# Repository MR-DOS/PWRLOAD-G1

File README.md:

# PWRLOAD-G1
DC constant current / constant power digitally controlled load, bachelor thesis in 2017

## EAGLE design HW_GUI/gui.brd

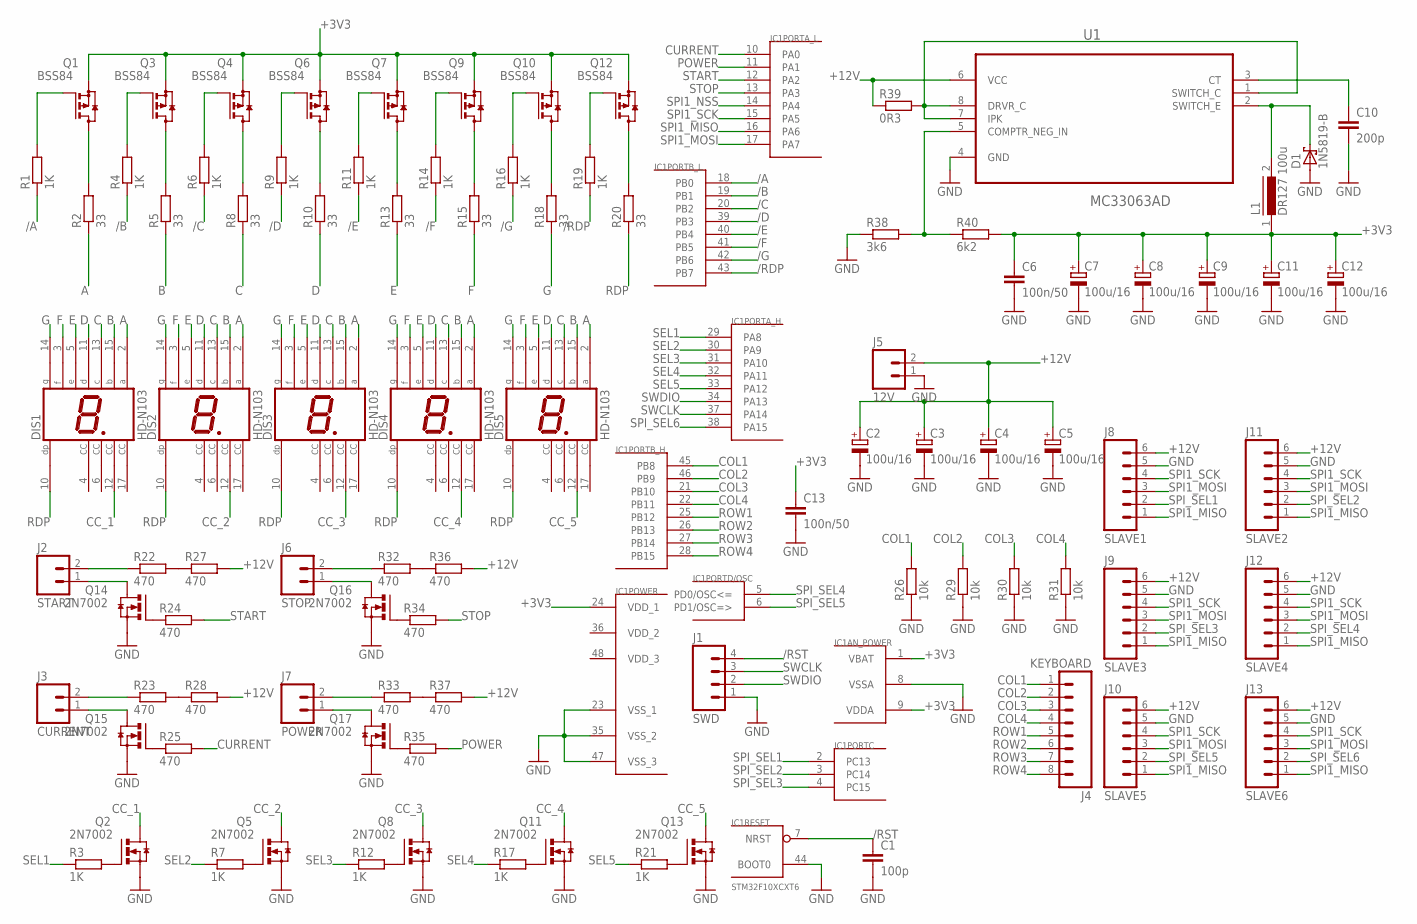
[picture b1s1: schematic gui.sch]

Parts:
C1: 100p; C0805
C2, C3, C4, C5, C7, C8, C9, C11, C12: 100u/16; 153CLV-0605
C6, C13: 100n/50; C0805
C10: 200p; C0805
D1: 1N5819-B; DO41-7.6
DIS1, DIS2, DIS3, DIS4, DIS5: HD-N103; HDSP-Q
IC1: STM32F10XCXT6; TQFP48
J1: SWD; 1X04_SMD_STRAIGHT_COMBO
J2: START; MOLEX-1X2_LOCK
J3: CURRENT; MOLEX-1X2_LOCK
J4: KEYBOARD; 1X08_LOCK_LONGPADS
J5: 12V; MOLEX-1X2_LOCK
J6: STOP; MOLEX-1X2_LOCK
J7: POWER; MOLEX-1X2_LOCK
J8: SLAVE1; MOLEX-1X6_LOCK
J9: SLAVE3; MOLEX-1X6_LOCK
J10: SLAVE5; MOLEX-1X6_LOCK
J11: SLAVE2; MOLEX-1X6_LOCK
J12: SLAVE4; MOLEX-1X6_LOCK
J13: SLAVE6; MOLEX-1X6_LOCK
L1: DR127 100u; DR127
Q1, Q3, Q4, Q6, Q7, Q9, Q10, Q12: BSS84; SOT23
Q2, Q5, Q8, Q11, Q13, Q14, Q15, Q16, Q17: 2N7002; SOT23-BEC
R1, R3, R4, R6, R7, R9, R11, R12, R14, R16, R17, R19, R21: 1K; R0805
R2, R5, R8, R10, R13, R15, R18, R20: 33; R0805
R22, R23, R24, R25, R27, R28, R32, R33, R34, R35, R36, R37: 470; R0805
R26, R29, R30, R31: 10k; R0805
R38: 3k6; R0805
R39: 0R3; R0805
R40: 6k2; R0805
U1: MC33063AD; SOIC127P600X175-8N

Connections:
+3V3: C6.1, C7.+, C8.+, C9.+, C11.+, C12.+, C13.1, IC1.1 (VBAT), IC1.9 (VDDA), IC1.24 (VDD_1), L1.1, Q1.2 (S), Q3.2 (S), Q4.2 (S), Q6.2 (S), Q7.2 (S), Q9.2 (S), Q10.2 (S), Q12.2 (S), R40.2
+12V: C2.+, C3.+, C4.+, C5.+, J5.2, J8.6, J9.6, J10.6, J11.6, J12.6, J13.6, R27.2, R28.2, R36.2, R37.2, R39.1, U1.6 (VCC)
/A: IC1.18 (PB0), R1.1
/B: IC1.19 (PB1), R4.1
/C: IC1.20 (PB2), R6.1
/D: IC1.39 (PB3), R9.1
/E: IC1.40 (PB4), R11.1
/F: IC1.41 (PB5), R14.1
/G: IC1.42 (PB6), R16.1
/RDP: IC1.43 (PB7), R19.1
/RST: C1.1, IC1.7 (NRST), J1.4
A: DIS1.2 (A), DIS2.2 (A), DIS3.2 (A), DIS4.2 (A), DIS5.2 (A), R2.1
B: DIS1.15 (B), DIS2.15 (B), DIS3.15 (B), DIS4.15 (B), DIS5.15 (B), R5.1
C: DIS1.13 (C), DIS2.13 (C), DIS3.13 (C), DIS4.13 (C), DIS5.13 (C), R8.1
CC_1: DIS1.12 (CC), Q2.C (D)
CC_2: DIS2.12 (CC), Q5.C (D)
CC_3: DIS3.12 (CC), Q8.C (D)
CC_4: DIS4.12 (CC), Q11.C (D)
CC_5: DIS5.12 (CC), Q13.C (D)
COL1: IC1.45 (PB8), J4.1, R26.2
COL2: IC1.46 (PB9), J4.2, R29.2
COL3: IC1.21 (PB10), J4.3, R30.2
COL4: IC1.22 (PB11), J4.4, R31.2
CURRENT: IC1.10 (PA0), R25.2
D: DIS1.11 (D), DIS2.11 (D), DIS3.11 (D), DIS4.11 (D), DIS5.11 (D), R10.1
E: DIS1.5 (E), DIS2.5 (E), DIS3.5 (E), DIS4.5 (E), DIS5.5 (E), R13.1
F: DIS1.3 (F), DIS2.3 (F), DIS3.3 (F), DIS4.3 (F), DIS5.3 (F), R15.1
G: DIS1.14 (G), DIS2.14 (G), DIS3.14 (G), DIS4.14 (G), DIS5.14 (G), R18.1
GND: C1.2, C2.-, C3.-, C4.-, C5.-, C6.2, C7.-, C8.-, C9.-, C10.2, C11.-, C12.-, C13.2, D1.A, IC1.8 (VSSA), IC1.23 (VSS_1), IC1.35 (VSS_2), IC1.44 (BOOT0), IC1.47 (VSS_3), J1.1, J5.1, J8.5, J9.5, J10.5, J11.5, J12.5, J13.5, Q2.E (S), Q5.E (S), Q8.E (S), Q11.E (S), Q13.E (S), Q14.E (S), Q15.E (S), Q16.E (S), Q17.E (S), R26.1, R29.1, R30.1, R31.1, R38.1, U1.4 (GND)
N3: Q8.B (G), R12.2
unnamed: Q1.3 (D), R2.2
unnamed: Q3.3 (D), R5.2
unnamed: Q4.3 (D), R8.2
unnamed: Q6.3 (D), R10.2
unnamed: Q7.3 (D), R13.2
unnamed: Q9.3 (D), R15.2
unnamed: Q10.3 (D), R18.2
unnamed: Q12.3 (D), R20.2
unnamed: Q11.B (G), R17.2
unnamed: Q2.B (G), R3.2
unnamed: Q5.B (G), R7.2
unnamed: Q13.B (G), R21.2
unnamed: Q12.1 (G), R19.2
unnamed: Q10.1 (G), R16.2
unnamed: Q9.1 (G), R14.2
unnamed: Q7.1 (G), R11.2
unnamed: Q6.1 (G), R9.2
unnamed: Q4.1 (G), R6.2
unnamed: Q3.1 (G), R4.2
unnamed: Q1.1 (G), R1.2
unnamed: J3.1, Q15.C (D)
unnamed: J7.1, Q17.C (D)
unnamed: J3.2, R23.1
unnamed: R23.2, R28.1
unnamed: J7.2, R33.1
unnamed: R33.2, R37.1
unnamed: J2.1, Q14.C (D)
unnamed: J2.2, R22.1
unnamed: R22.2, R27.1
unnamed: J6.1, Q16.C (D)
unnamed: J6.2, R32.1
unnamed: R32.2, R36.1
unnamed: R38.2, R40.1, U1.5 (COMPTR_NEG_IN)
unnamed: C10.1, U1.3 (CT)
unnamed: Q14.B (G), R24.1
unnamed: R39.2, U1.1 (SWITCH_C), U1.7 (IPK), U1.8 (DRVR_C)
unnamed: D1.C, L1.2, U1.2 (SWITCH_E)
unnamed: Q15.B (G), R25.1
unnamed: Q16.B (G), R34.1
unnamed: Q17.B (G), R35.1
POWER: IC1.11 (PA1), R35.2
RDP: DIS1.10 (DP), DIS2.10 (DP), DIS3.10 (DP), DIS4.10 (DP), DIS5.10 (DP), R20.1
ROW1: IC1.25 (PB12), J4.5
ROW2: IC1.26 (PB13), J4.6
ROW3: IC1.27 (PB14), J4.7
ROW4: IC1.28 (PB15), J4.8
SEL1: IC1.29 (PA8), R3.1
SEL2: IC1.30 (PA9), R7.1
SEL3: IC1.31 (PA10), R12.1
SEL4: IC1.32 (PA11), R17.1
SEL5: IC1.33 (PA12), R21.1
SPI1_MISO: IC1.16 (PA6), J8.1, J9.1, J10.1, J11.1, J12.1, J13.1
SPI1_MOSI: IC1.17 (PA7), J8.3, J9.3, J10.3, J11.3, J12.3, J13.3
SPI1_NSS: IC1.14 (PA4)
SPI1_SCK: IC1.15 (PA5), J8.4, J9.4, J10.4, J11.4, J12.4, J13.4
SPI_SEL1: IC1.2 (PC13), J8.2
SPI_SEL2: IC1.3 (PC14), J11.2
SPI_SEL3: IC1.4 (PC15), J9.2
SPI_SEL4: IC1.5 (PD0/OSC<=), J12.2
SPI_SEL5: IC1.6 (PD1/OSC=>), J10.2
SPI_SEL6: IC1.38 (PA15), J13.2
START: IC1.12 (PA2), R24.2
STOP: IC1.13 (PA3), R34.2
SWCLK: IC1.37 (PA14), J1.3
SWDIO: IC1.34 (PA13), J1.2
VDD_2: IC1.36 (VDD_2)
VDD_3: IC1.48 (VDD_3)

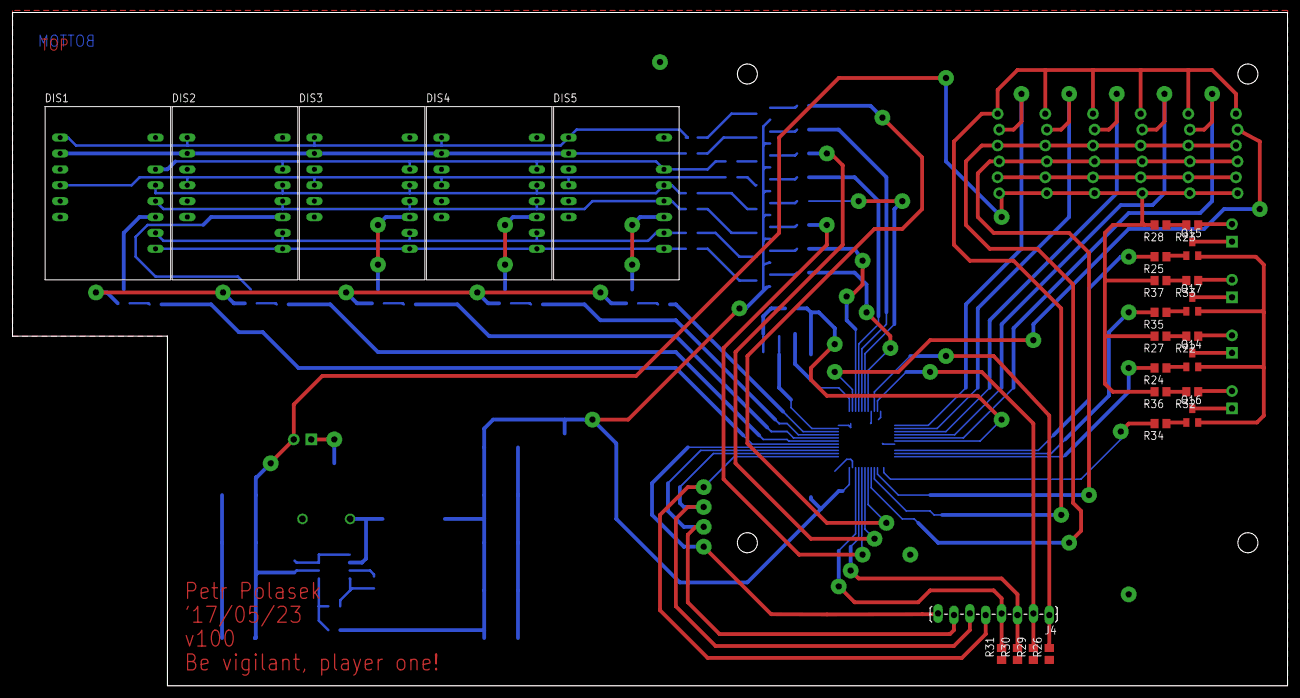
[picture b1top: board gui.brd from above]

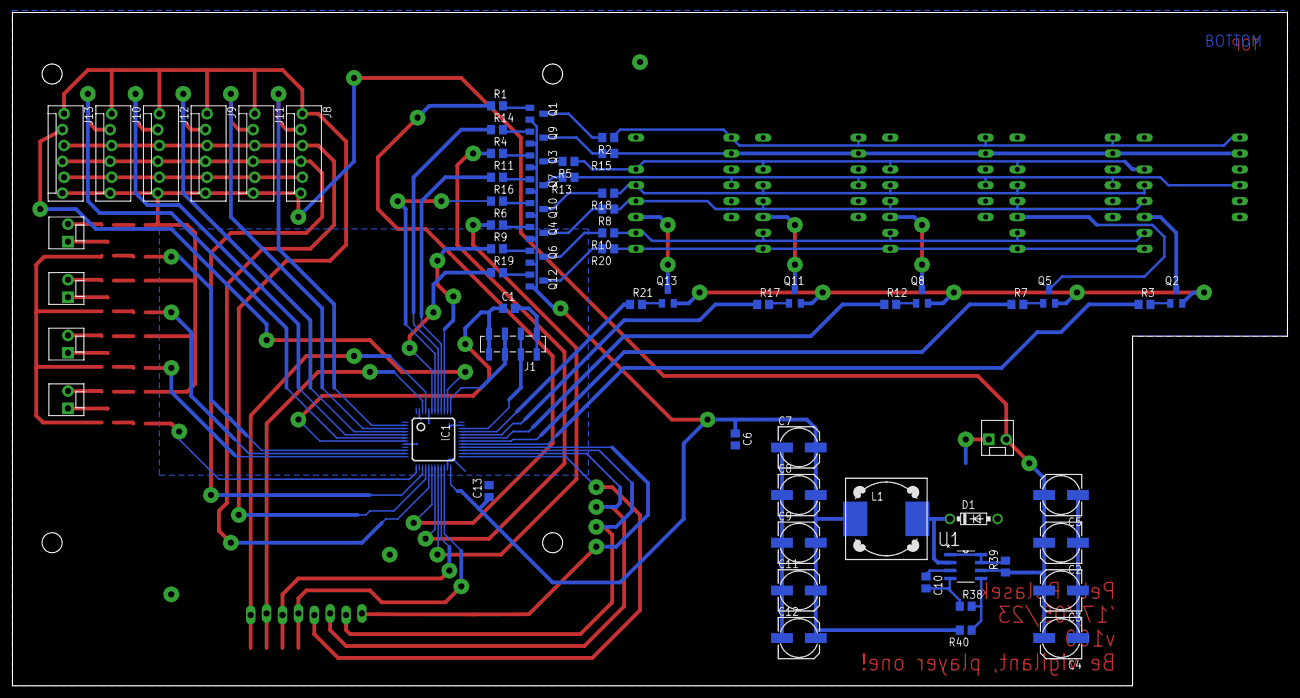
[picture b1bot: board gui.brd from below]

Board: 2 copper layers, 203.8 x 107.6 mm, 92 parts (66 on the bottom side), 94 nets.

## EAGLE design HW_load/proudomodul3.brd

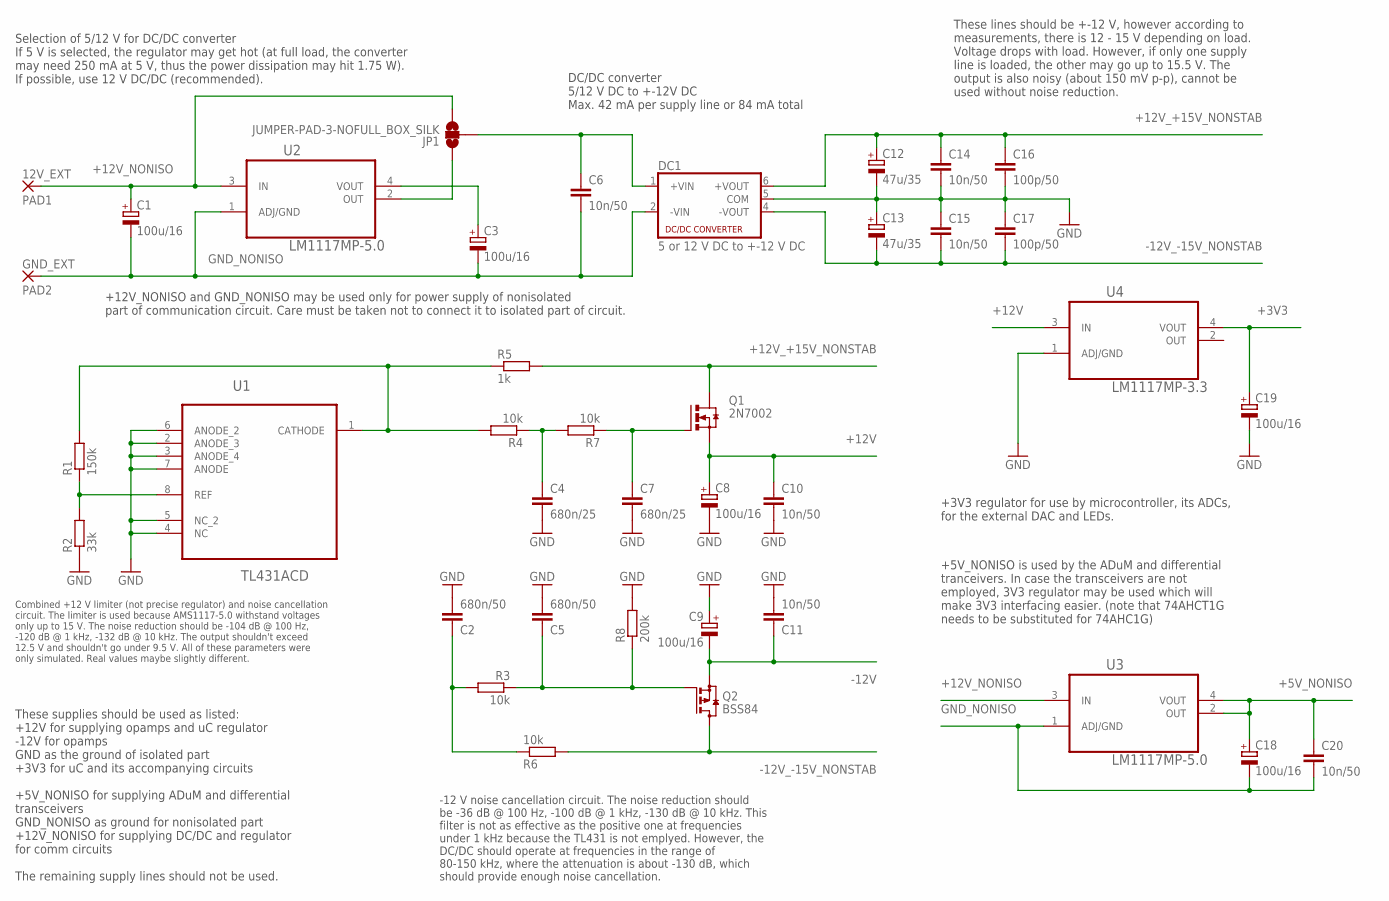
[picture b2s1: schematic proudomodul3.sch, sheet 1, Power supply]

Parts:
C1, C3, C8, C9, C18, C19: 100u/16; 153CLV-0605
C2, C5: 680n/50; C0805
C4, C7: 680n/25; C0805
C6, C10, C11, C14, C15, C20: 10n/50; C0805
C12, C13: 47u/35; 153CLV-0605
C16, C17: 100p/50; C0805
DC1: 5 or 12 V DC to +-12 V DC; NMA
JP1: JUMPER-PAD-3-NOFULL_BOX_SILK; PAD-JUMPER-3-NO_YES_SILK_FULL_BOX
PAD1: 12V_EXT; 2,15/1,0
PAD2: GND_EXT; 2,15/1,0
Q1: 2N7002; SOT23-BEC
Q2: BSS84; SOT23
R1: 150k; R0805
R2: 33k; R0805
R3, R4, R6, R7: 10k; R0805
R5: 1k; R0805
R8: 200k; R0805
U1: TL431ACD; SOIC127P600X175-8N
U2, U3: LM1117MP-5.0; SOT230P696X180-4N
U4: LM1117MP-3.3; SOT230P696X180-4N

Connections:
+3V3: C19.+, U4.4 (VOUT); also elsewhere on the board
+5V_NONISO: C18.+, C20.1, U3.2 (OUT), U3.4 (VOUT); also elsewhere on the board
+12V: C8.+, C10.1, Q1.E (S), U4.3 (IN); also elsewhere on the board
+12V_+15V_NONSTAB: C12.+, C14.1, C16.1, DC1.6 (+VOUT), Q1.C (D), R5.2
+12V_NONISO: C1.+, JP1.3, PAD1.1, U2.3 (IN), U3.3 (IN); also elsewhere on the board
-12V: C9.-, C11.1, Q2.2 (S); also elsewhere on the board
-12V_-15V_NONSTAB: C13.-, C15.2, C17.2, DC1.4 (-VOUT), Q2.3 (D), R6.2
GND: C2.2, C4.2, C5.2, C7.2, C8.-, C9.+, C10.2, C11.2, C12.-, C13.+, C14.2, C15.1, C16.2, C17.1, C19.-, DC1.5 (COM), R2.1, R8.2, U1.2 (ANODE_3), U1.3 (ANODE_4), U1.4 (NC), U1.5 (NC_2), U1.6 (ANODE_2), U1.7 (ANODE), U4.1 (ADJ/GND); also elsewhere on the board
GND_NONISO: C1.-, C3.-, C6.2, C18.-, C20.2, DC1.2 (-VIN), PAD2.1, U2.1 (ADJ/GND), U3.1 (ADJ/GND); also elsewhere on the board
unnamed: C4.1, R4.1, R7.2
unnamed: C6.1, DC1.1 (+VIN), JP1.2
unnamed: R1.1, R2.2, U1.8 (REF)
unnamed: R1.2, R4.2, R5.1, U1.1 (CATHODE)
unnamed: C7.1, Q1.B (G), R7.1
unnamed: C2.1, R3.2, R6.1
unnamed: C5.1, Q2.1 (G), R3.1, R8.1
unnamed: JP1.1, U2.2 (OUT)
unnamed: C3.+, U2.4 (VOUT)

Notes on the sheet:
DC/DC converter 5/12 V DC to +-12V DC Max. 42 mA per supply line or 84 mA total
Selection of 5/12 V for DC/DC converter If 5 V is selected, the regulator may get hot (at full load, the converter may need 250 mA at 5 V, thus the power dissipation may hit 1.75 W). If possible, use 12 V DC/DC (recommended).
These lines should be +-12 V, however according to measurements, there is 12 - 15 V depending on load. Voltage drops with load. However, if only one supply line is loaded, the other may go up to 15.5 V. The output is also noisy (about 150 mV p-p), cannot be used without noise reduction.
Combined +12 V limiter (not precise regulator) and noise cancellation circuit. The limiter is used because AMS1117-5.0 withstand voltages only up to 15 V. The noise reduction should be -104 dB @ 100 Hz, -120 dB @ 1 kHz, -132 dB @ 10 kHz. The output shouldn't exceed 12.5 V and shouldn't go under 9.5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
-12 V noise cancellation circuit. The noise reduction should be -36 dB @ 100 Hz, -100 dB @ 1 kHz, -130 dB @ 10 kHz. This filter is not as effective as the positive one at frequencies under 1 kHz because the TL431 is not emplyed. However, the DC/DC should operate at frequencies in the range of 80-15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
+12V_NONISO and GND_NONISO may be used only for power supply of nonisolated part of communication circuit. Care must be taken not to connect it to isolated part of circuit.
+3V3 regulator for use by microcontroller, its ADCs, for the external DAC and LEDs.
These supplies should be used as listed: +12V for supplying opamps and uC regulator -12V for opamps GND as the ground of isolated part +3V3 for uC and its accompanying circuits +5V_NONISO for supplying ADuM and differential transceivers GND_NONISO as ground for nonisolated part +12V_NONISO for supp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
+5V_NONISO is used by the ADuM and differential tranceivers. In case the transceivers are not employed, 3V3 regulator may be used which will make 3V3 interfacing easier. (note that 74AHCT1G needs to be substituted for 74AHC1G)

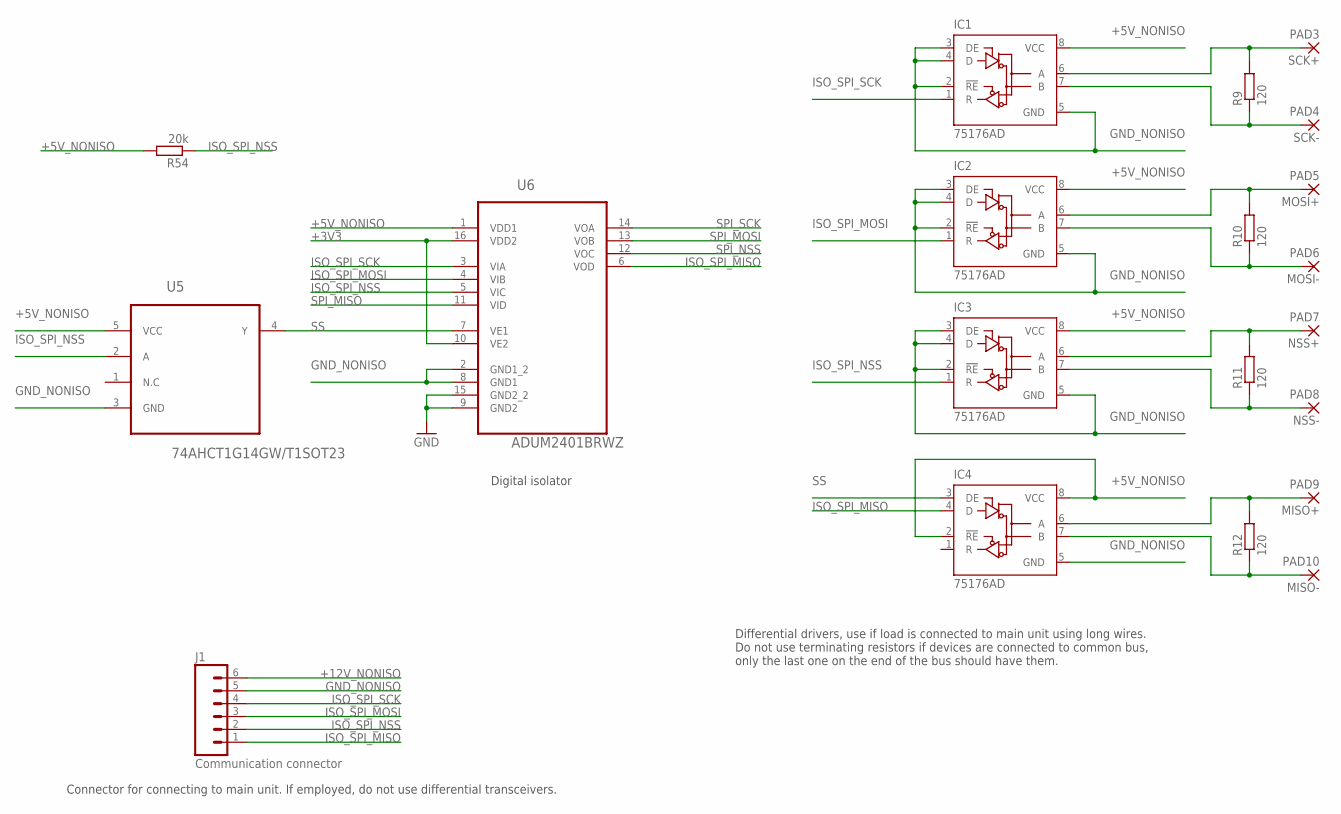
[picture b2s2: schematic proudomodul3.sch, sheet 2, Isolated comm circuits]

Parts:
IC1, IC2, IC3, IC4: 75176AD; D_R-PDSO-G8
J1: Communication connector; MOLEX-1X6-RA_LOCK
PAD3: SCK+; 2,15/1,0
PAD4: SCK-; 2,15/1,0
PAD5: MOSI+; 2,15/1,0
PAD6: MOSI-; 2,15/1,0
PAD7: NSS+; 2,15/1,0
PAD8: NSS-; 2,15/1,0
PAD9: MISO+; 2,15/1,0
PAD10: MISO-; 2,15/1,0
R9, R10, R11, R12: 120; R0805
R54: 20k; R0805
U5: 74AHCT1G14GW/T1SOT23; SOT23-5L
U6: ADUM2401BRWZ; SOIC127P1032X265-16N

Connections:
+3V3: U6.10 (VE2), U6.16 (VDD2); also elsewhere on the board
+5V_NONISO: IC1.8 (VCC), IC2.8 (VCC), IC3.8 (VCC), IC4.2 (!RE), IC4.8 (VCC), R54.2, U5.5 (VCC), U6.1 (VDD1); also elsewhere on the board
+12V_NONISO: J1.6; also elsewhere on the board
GND: U6.9 (GND2), U6.15 (GND2_2); also elsewhere on the board
GND_NONISO: IC1.2 (!RE), IC1.3 (DE), IC1.4 (D), IC1.5 (GND), IC2.2 (!RE), IC2.3 (DE), IC2.4 (D), IC2.5 (GND), IC3.2 (!RE), IC3.3 (DE), IC3.4 (D), IC3.5 (GND), IC4.5 (GND), J1.5, U5.3 (GND), U6.2 (GND1_2), U6.8 (GND1); also elsewhere on the board
ISO_SPI_MISO: IC4.4 (D), J1.1, U6.6 (VOD)
ISO_SPI_MOSI: IC2.1 (R), J1.3, U6.4 (VIB)
ISO_SPI_NSS: IC3.1 (R), J1.2, R54.1, U5.2 (A), U6.5 (VIC)
ISO_SPI_SCK: IC1.1 (R), J1.4, U6.3 (VIA)
unnamed: IC4.6 (A), PAD9.1, R12.2
unnamed: IC4.7 (B), PAD10.1, R12.1
unnamed: IC3.6 (A), PAD7.1, R11.2
unnamed: IC3.7 (B), PAD8.1, R11.1
unnamed: IC2.6 (A), PAD5.1, R10.2
unnamed: IC2.7 (B), PAD6.1, R10.1
unnamed: IC1.7 (B), PAD4.1, R9.1
unnamed: IC1.6 (A), PAD3.1, R9.2
SPI_MISO: U6.11 (VID); also elsewhere on the board
SPI_MOSI: U6.13 (VOB); also elsewhere on the board
SPI_NSS: U6.12 (VOC); also elsewhere on the board
SPI_SCK: U6.14 (VOA); also elsewhere on the board
SS: IC4.3 (DE), U5.4 (Y), U6.7 (VE1)

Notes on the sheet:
Differential drivers, use if load is connected to main unit using long wires. Do not use terminating resistors if devices are connected to common bus, only the last one on the end of the bus should have them.
Digital isolator
Connector for connecting to main unit. If employed, do not use differential transceivers.

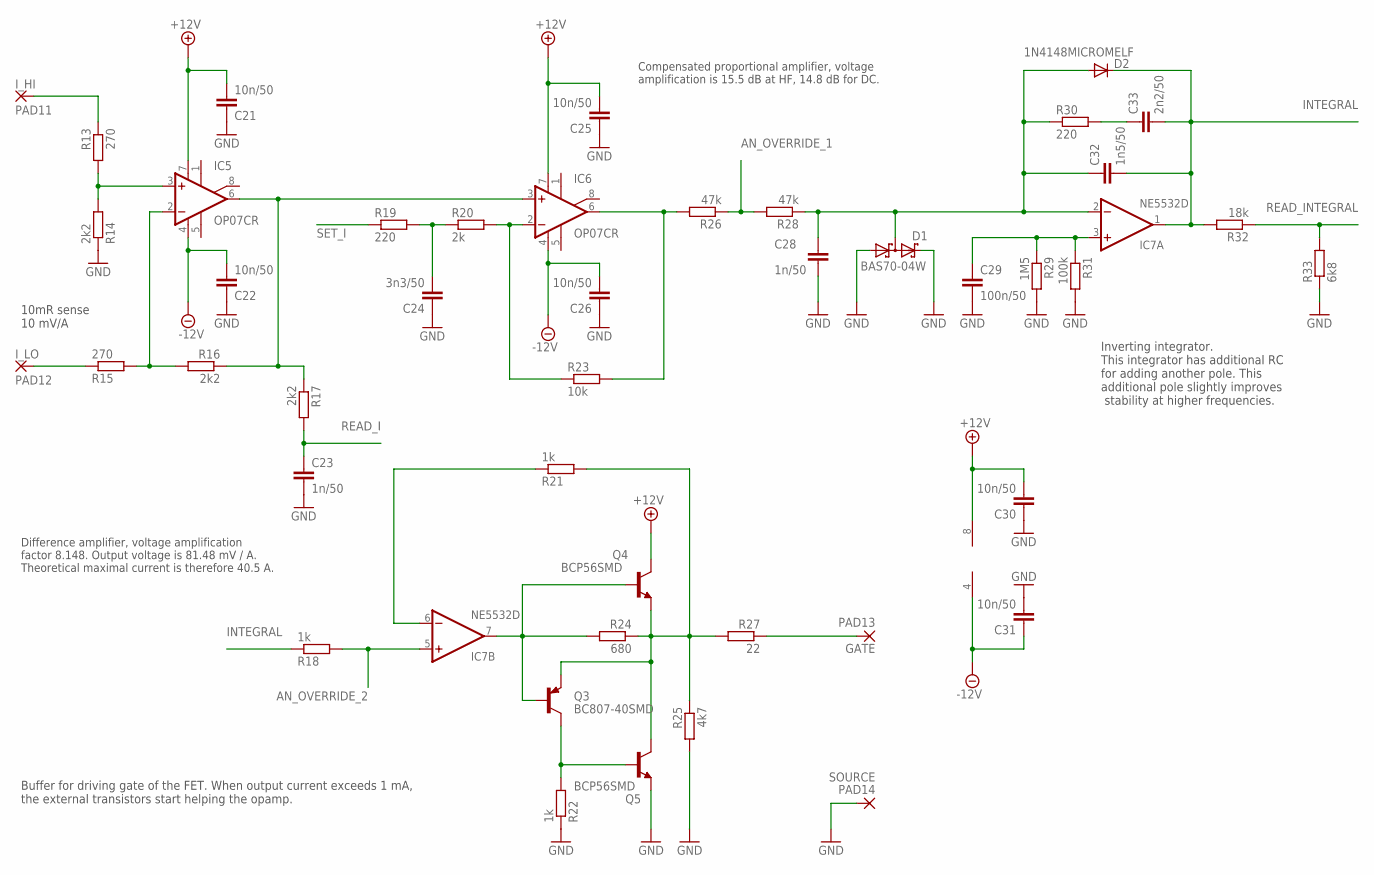
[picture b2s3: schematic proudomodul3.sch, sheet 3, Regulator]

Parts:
C21, C22, C25, C26, C30, C31: 10n/50; C0805
C23, C28: 1n/50; C0805
C24: 3n3/50; C0805
C29: 100n/50; C0805
C32: 1n5/50; C0805
C33: 2n2/50; C0805
D1: BAS70-04W; SOT323
D2: 1N4148MICROMELF; MICROMELF-W
IC5, IC6: OP07CR; SO08
IC7: NE5532D; SO08
PAD11: I_HI; 2,15/1,0
PAD12: I_LO; 2,15/1,0
PAD13: GATE; 2,15/1,0
PAD14: SOURCE; 2,15/1,0
Q3: BC807-40SMD; SOT23-BEC
Q4, Q5: BCP56SMD; SOT223
R13, R15: 270; R0805
R14, R16, R17: 2k2; R0805
R18, R21, R22: 1k; R0805
R19, R30: 220; R0805
R20: 2k; R0805
R23: 10k; R0805
R24: 680; R0805
R25: 4k7; R0805
R26, R28: 47k; R0805
R27: 22; R0805
R29: 1M5; R0805
R31: 100k; R0805
R32: 18k; R0805
R33: 6k8; R0805

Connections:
+12V: C21.2, C25.2, C30.2, IC5.7 (V+), IC6.7 (V+), IC7.8 (V+), Q4.2 (C), Q4.4 (C); also elsewhere on the board
-12V: C22.2, C26.2, C31.1, IC5.4 (V-), IC6.4 (V-), IC7.4 (V-); also elsewhere on the board
AN_OVERRIDE_1: R26.1, R28.2; also elsewhere on the board
AN_OVERRIDE_2: IC7.5 (+IN), R18.2; also elsewhere on the board
GND: C21.1, C22.1, C23.2, C24.1, C25.1, C26.1, C28.2, C29.2, C30.1, C31.2, D1.1 (A1), D1.2 (C2), PAD14.1, Q5.3 (E), R14.1, R22.1, R25.2, R29.2, R31.2, R33.1; also elsewhere on the board
INTEGRAL: C32.2, C33.2, D2.C, IC7.1 (OUT), R18.1, R32.2
unnamed: C33.1, R30.2
unnamed: PAD11.1, R13.1
unnamed: PAD13.1, R27.1
unnamed: Q3.E, Q4.3 (E), Q5.2 (C), Q5.4 (C), R21.2, R24.1, R25.1, R27.2
unnamed: IC7.7 (OUT), Q3.B, Q4.1 (B), R24.2
unnamed: IC5.3 (+IN), R13.2, R14.2
unnamed: PAD12.1, R15.1
unnamed: IC5.2 (-IN), R15.2, R16.2
unnamed: C28.1, C32.1, D1.3 (C1A2), D2.A, IC7.2 (-IN), R28.1, R30.1
unnamed: C29.1, IC7.3 (+IN), R29.1, R31.1
unnamed: IC6.6 (OUT), R23.2, R26.2
unnamed: Q3.C, Q5.1 (B), R22.2
unnamed: IC7.6 (-IN), R21.1
unnamed: IC6.2 (-IN), R20.2, R23.1
unnamed: IC5.6 (OUT), IC6.3 (+IN), R16.1, R17.1
unnamed: C24.2, R19.2, R20.1
READ_I: C23.1, R17.2; also elsewhere on the board
READ_INTEGRAL: R32.1, R33.2; also elsewhere on the board
SET_I: R19.1; also elsewhere on the board

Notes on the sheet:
10mR sense 10 mV/A
Compensated proportional amplifier, voltage amplification is 15.5 dB at HF, 14.8 dB for DC.
Inverting integrator. This integrator has additional RC for adding another pole. This additional pole slightly improves stability at higher frequencies.
Buffer for driving gate of the FET. When output current exceeds 1 mA, the external transistors start helping the opamp.
Difference amplifier, voltage amplification factor 8.148. Output voltage is 81.48 mV / A. Theoretical maximal current is therefore 40.5 A.

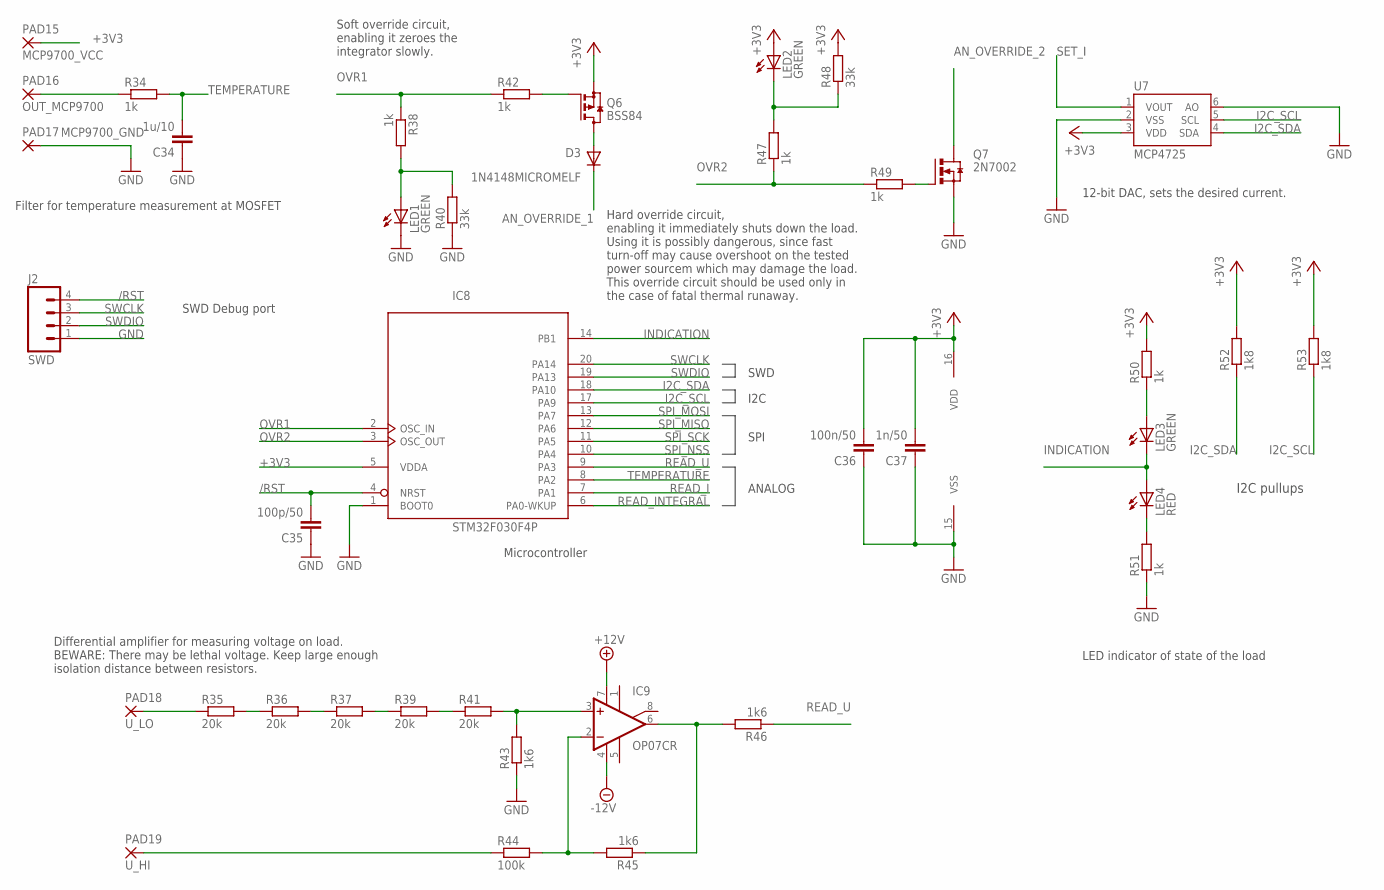
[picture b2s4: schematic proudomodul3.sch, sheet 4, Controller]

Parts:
C34: 1u/10; C0805
C35: 100p/50; C0805
C36: 100n/50; C0805
C37: 1n/50; C0805
D3: 1N4148MICROMELF; MICROMELF-W
IC8: STM32F030F4P; TSSOP20-I
IC9: OP07CR; SO08
J2: SWD; 1X04_SMD_STRAIGHT_COMBO
LED1, LED2, LED3: GREEN; SML0603
LED4: RED; SML0603
PAD15: MCP9700_VCC; 2,15/1,0
PAD16: OUT_MCP9700; 2,15/1,0
PAD17: MCP9700_GND; 2,15/1,0
PAD18: U_LO; 2,15/1,0
PAD19: U_HI; 2,15/1,0
Q6: BSS84; SOT23
Q7: 2N7002; SOT23-BEC
R34, R38, R42, R47, R49, R50, R51: 1k; R0805
R35, R36, R37, R39, R41: 20k; R0805
R40, R48: 33k; R0805
R43, R45, R46: 1k6; R0805
R44: 100k; R0805
R52, R53: 1k8; R0805
U7: MCP4725; SOT23-6

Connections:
+3V3: C36.2, C37.2, IC8.5 (VDDA), IC8.16 (VDD), LED2.A, PAD15.1, Q6.2 (S), R48.2, R50.2, R52.2, R53.2, U7.3 (VDD); also elsewhere on the board
+12V: IC9.7 (V+); also elsewhere on the board
-12V: IC9.4 (V-); also elsewhere on the board
/RST: C35.2, IC8.4 (NRST), J2.4
AN_OVERRIDE_1: D3.C; also elsewhere on the board
AN_OVERRIDE_2: Q7.C (D); also elsewhere on the board
GND: C34.1, C35.1, C36.1, C37.1, IC8.1 (BOOT0), IC8.15 (VSS), J2.1, LED1.C, PAD17.1, Q7.E (S), R40.1, R43.1, R51.1, U7.2 (VSS), U7.6 (AO); also elsewhere on the board
I2C_SCL: IC8.17 (PA9), R53.1, U7.5 (SCL)
I2C_SDA: IC8.18 (PA10), R52.1, U7.4 (SDA)
INDICATION: IC8.14 (PB1), LED3.C, LED4.A
unnamed: LED1.A, R38.2, R40.2
unnamed: Q6.1 (G), R42.2
unnamed: Q7.B (G), R49.2
unnamed: D3.A, Q6.3 (D)
unnamed: LED2.C, R47.2, R48.1
unnamed: PAD16.1, R34.1
unnamed: IC9.3 (+IN), R41.2, R43.2
unnamed: LED3.A, R50.1
unnamed: IC9.2 (-IN), R44.2, R45.2
unnamed: IC9.6 (OUT), R45.1, R46.2
unnamed: R39.2, R41.1
unnamed: R37.2, R39.1
unnamed: R36.2, R37.1
unnamed: R35.2, R36.1
unnamed: PAD19.1, R44.1
unnamed: PAD18.1, R35.1
unnamed: LED4.C, R51.2
OVR1: IC8.2 (OSC_IN), R38.1, R42.1
OVR2: IC8.3 (OSC_OUT), R47.1, R49.1
READ_I: IC8.7 (PA1); also elsewhere on the board
READ_INTEGRAL: IC8.6 (PA0-WKUP); also elsewhere on the board
READ_U: IC8.9 (PA3), R46.1
SET_I: U7.1 (VOUT); also elsewhere on the board
SPI_MISO: IC8.12 (PA6); also elsewhere on the board
SPI_MOSI: IC8.13 (PA7); also elsewhere on the board
SPI_NSS: IC8.10 (PA4); also elsewhere on the board
SPI_SCK: IC8.11 (PA5); also elsewhere on the board
SWCLK: IC8.20 (PA14), J2.3
SWDIO: IC8.19 (PA13), J2.2
TEMPERATURE: C34.2, IC8.8 (PA2), R34.2

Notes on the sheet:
I2C
SWD
SPI
ANALOG
Filter for temperature measurement at MOSFET
Soft override circuit, enabling it zeroes the integrator slowly.
Hard override circuit, enabling it immediately shuts down the load. Using it is possibly dangerous, since fast turn-off may cause overshoot on the tested power sourcem which may damage the load. This override circuit should be used only in the case of fatal thermal runaway.
12-bit DAC, sets the desired current.
SWD Debug port
I2C pullups
Differential amplifier for measuring voltage on load. BEWARE: There may be lethal voltage. Keep large enough isolation distance between resistors.
Microcontroller
LED indicator of state of the load

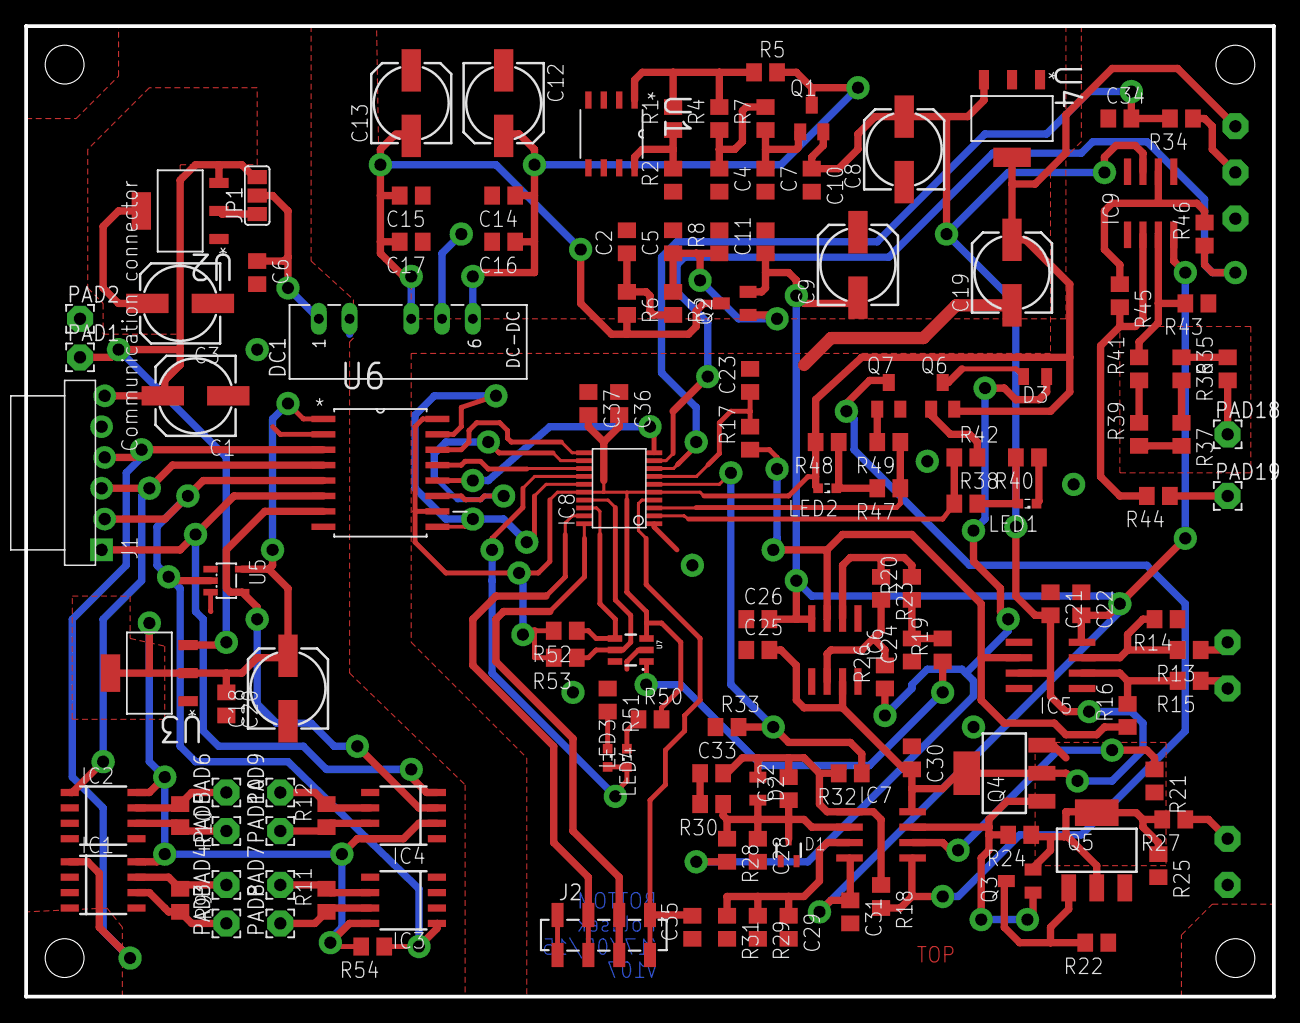
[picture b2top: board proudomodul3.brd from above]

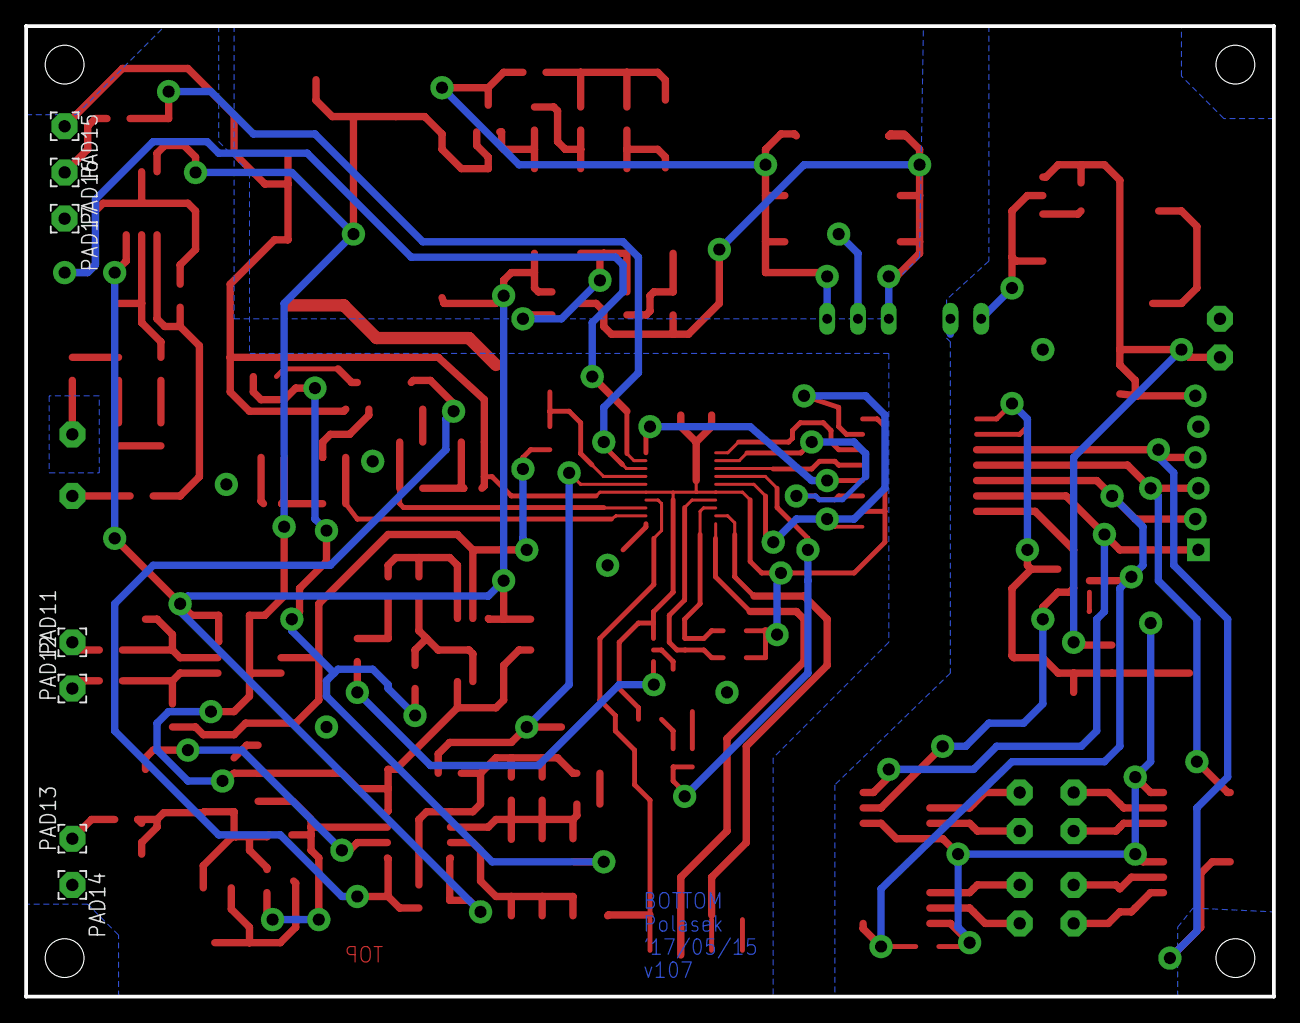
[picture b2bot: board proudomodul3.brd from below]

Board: 2 copper layers, 102.9 x 80.0 mm, 143 parts (7 on the bottom side), 84 nets.

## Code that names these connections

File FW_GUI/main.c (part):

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
#define		digit_pins		(nA_pin | nB_pin | nC_pin | nD_pin | nE_pin | nF_pin | nG_pin | nRDP_pin)

#define		SEL1					GPIO_Pin_8
#define		SEL2					GPIO_Pin_9
#define		SEL3					GPIO_Pin_10
#define		SEL4					GPIO_Pin_11
#define		SEL5					GPIO_Pin_12

#define		select_pins		(SEL1 | SEL2 | SEL3 | SEL4 | SEL5)

#define		CURRENT_pin		GPIO_Pin_0
#define		POWER_pin			GPIO_Pin_1
#define		START_pin			GPIO_Pin_2
#define		STOP_pin			GPIO_Pin_3

#define		MODE_pins			(CURRENT_pin | POWER_pin)
#define		STATE_pins		(START_pin 	 | STOP_pin)
#define		LED_pins			(CURRENT_pin | POWER_pin | START_pin | STOP_pin)

#define		COL1					GPIO_Pin_8
#define		COL2					GPIO_Pin_9
#define		COL3					GPIO_Pin_10
#define		COL4					GPIO_Pin_11

#define		COLUMN_pins	  (COL1 | COL2 | COL3 | COL4)

#define		ROW1					GPIO_Pin_12
#define		ROW2					GPIO_Pin_13
#define		ROW3					GPIO_Pin_14
#define		ROW4					GPIO_Pin_15

#define		ROW_pins			(ROW1 | ROW2 | ROW3 | ROW4)

#define		KEYPAD_pins		(COLUMN_pins | ROW_pins)

#define		SPI_SCK_pin		GPIO_Pin_5
#define		SPI_MISO_pin	GPIO_Pin_6
#define		SPI_MOSI_pin	GPIO_Pin_7
#define		SPI_SEL2_pin	GPIO_Pin_13
#define		SPI_SEL3_pin	GPIO_Pin_15

#define		SPI_pins			(SPI_SCK_pin | SPI_MISO_pin | SPI_MOSI_pin)
#define		SPI_SEL_pins	(SPI_SEL2_pin | SPI_SEL3_pin)

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	GPIO_SetBits(GPIOB, digit_pins);
	
	GPIO_InitStruct.GPIO_Mode=GPIO_Mode_Out_PP;
	GPIO_InitStruct.GPIO_Pin = SEL1 | SEL2 | SEL3 | SEL4 | SEL5;
	GPIO_InitStruct.GPIO_Speed=GPIO_Speed_10MHz;
	GPIO_Init(GPIOA, &GPIO_InitStruct);	
	
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void ShowLEDs(void)
{
	GPIO_ResetBits(GPIOA, MODE_pins);
	GPIO_SetBits(GPIOA, (load_mode==const_i) ? CURRENT_pin : POWER_pin);
	
	GPIO_ResetBits(GPIOA, STATE_pins);
	GPIO_SetBits(GPIOA, (load_state==DISABLE) ? STOP_pin : START_pin);
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{
	GPIO_SetBits(GPIOB, digit_pins & (~(uint32_t) digit_segments[digit]));
	GPIO_ResetBits(GPIOB, (uint32_t) digit_segments[digit]);
	if (RDP==ENABLE) GPIO_ResetBits(GPIOB, nRDP_pin);
}

void SelectDigit(uint8_t digit)
{
	GPIO_ResetBits(GPIOA, select_pins);
	GPIO_SetBits(GPIOA, SEL5 >> digit);
}

void SPIInit(void)
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	SPI_InitTypeDef	SPI_InitStruct;
	
	GPIO_InitStruct.GPIO_Mode=GPIO_Mode_AF_PP;
	GPIO_InitStruct.GPIO_Pin = SPI_SCK_pin | SPI_MOSI_pin;
	GPIO_InitStruct.GPIO_Speed = GPIO_Speed_50MHz;
	GPIO_Init(GPIOA, &GPIO_InitStruct);	
	
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	GPIO_SetBits(GPIOC, SPI_SEL_pins);
	
	GPIO_InitStruct.GPIO_Mode = GPIO_Mode_IN_FLOATING;	
	GPIO_InitStruct.GPIO_Pin = SPI_MISO_pin;
	GPIO_Init(GPIOA, &GPIO_InitStruct);	
	
	SPI_StructInit(&SPI_InitStruct);
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	if (load_state==DISABLE) temp_cmd=0;
	while (SPI_I2S_GetFlagStatus(SPI1, SPI_I2S_FLAG_BSY)) {};
		
	GPIO_ResetBits(GPIOC, SPI_SEL3_pin);
	for (uint16_t tmp=0; tmp<50; tmp++) {}
	SPI_I2S_SendData(SPI1, temp_cmd);
	while (SPI_I2S_GetFlagStatus(SPI1, SPI_I2S_FLAG_BSY)) {};	
	for (uint16_t tmp=0; tmp<50; tmp++) {}
	GPIO_SetBits(GPIOC, SPI_SEL3_pin);
		
	GPIO_ResetBits(GPIOC, SPI_SEL2_pin);
	for (uint16_t tmp=0; tmp<50; tmp++) {}
	SPI_I2S_SendData(SPI1, temp_cmd);
	while (SPI_I2S_GetFlagStatus(SPI1, SPI_I2S_FLAG_BSY)) {};	
	for (uint16_t tmp=0; tmp<50; tmp++) {}
	GPIO_SetBits(GPIOC, SPI_SEL2_pin);		
}

int main(void)
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
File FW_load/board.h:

#ifndef __BOARD_H
#define __BOARD_H

#include <stdint.h>
#include "stm32f0xx.h"

#define SysTick_CLKSource_HCLK_Div8    ((uint32_t)0xFFFFFFFB)
#define SysTick_CLKSource_HCLK         ((uint32_t)0x00000004)
#define IS_SYSTICK_CLK_SOURCE(SOURCE)  (((SOURCE) == SysTick_CLKSource_HCLK) || \
                                       ((SOURCE) == SysTick_CLKSource_HCLK_Div8))

#define LED_PORT 							GPIOB
#define LED_PIN 							GPIO_Pin_1
#define LED_OK								ENABLE
#define LED_ERROR							DISABLE

#define	AN_PORT								GPIOA

#define READ_INTEGRAL_PORT		AN_PORT
#define READ_INTEGRAL_PIN 		GPIO_Pin_0
#define READ_I_PORT						AN_PORT
#define READ_I_PIN 						GPIO_Pin_1
#define TEMPERATURE_PORT			AN_PORT
#define	TEMPERATURE_PIN				GPIO_Pin_2
#define READ_U_PORT						AN_PORT
#define READ_U_PIN 						GPIO_Pin_3

#define OVR1_PORT							GPIOF
#define OVR1_PIN							GPIO_Pin_0
#define OVR2_PORT							GPIOF
#define OVR2_PIN							GPIO_Pin_1

#define PASTE_EVAL(x,y)				x##y
#define PASTE(x,y)						PASTE_EVAL(x,y)
#define GPIO_PIN_TEMPLATE			GPIO_Pin_

#define I2C_PORT							GPIOA
#define SCL_PIN_NUMBER				9
#define	SCL_PIN								PASTE(GPIO_PIN_TEMPLATE, SCL_PIN_NUMBER)
#define SDA_PIN_NUMBER				10
#define	SDA_PIN								PASTE(GPIO_PIN_TEMPLATE, SDA_PIN_NUMBER)

#define SPI_PORT							GPIOB
#define SPI_NSS_PIN_NUMBER		4
#define SPI_SCK_PIN_NUMBER		5
#define SPI_MISO_PIN_NUMBER		6
#define SPI_MOSI_PIN_NUMBER		7
#define	SPI_NSS_PIN						PASTE(GPIO_PIN_TEMPLATE, SPI_NSS_PIN_NUMBER)
#define	SPI_SCK_PIN						PASTE(GPIO_PIN_TEMPLATE, SPI_SCK_PIN_NUMBER)
#define	SPI_MISO_PIN					PASTE(GPIO_PIN_TEMPLATE, SPI_MISO_PIN_NUMBER)
#define	SPI_MOSI_PIN					PASTE(GPIO_PIN_TEMPLATE, SPI_MISO_PIN_NUMBER)

#define GENERAL_CALL_RESET		0x06
#define GENERAL_CALL_WAKEUP		0x09

#define MCP4725_ADDR					0xC0
		//the device code part of address of MCP4725, do not change

typedef enum
{
	NO_OVERRIDE, SOFT_OVERRIDE, HARD_OVERRIDE, COMPLETE_OVERRIDE
} OverrideState;

void BoardInit(void);
void DAC_Write_Fast(uint16_t DAC_value);
void ChangeLEDState(FunctionalState NewState);
uint16_t ADC_Read(uint32_t channel);
//void SysTick_CLKSourceConfig(uint32_t SysTick_CLKSource);
void SystemCoreClockUpdate(void);
void OverrideMode(OverrideState mode);
void SetCurrent(int32_t current);

#endif //__BOARD_H

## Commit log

2022-01-06 Added files of the project.

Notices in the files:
parts and their libraries:
SparkFun-Connectors: Licensing: Creative Commons ShareAlike 4.0 International - https://creativecommons.org/licenses/by-sa/4.0
